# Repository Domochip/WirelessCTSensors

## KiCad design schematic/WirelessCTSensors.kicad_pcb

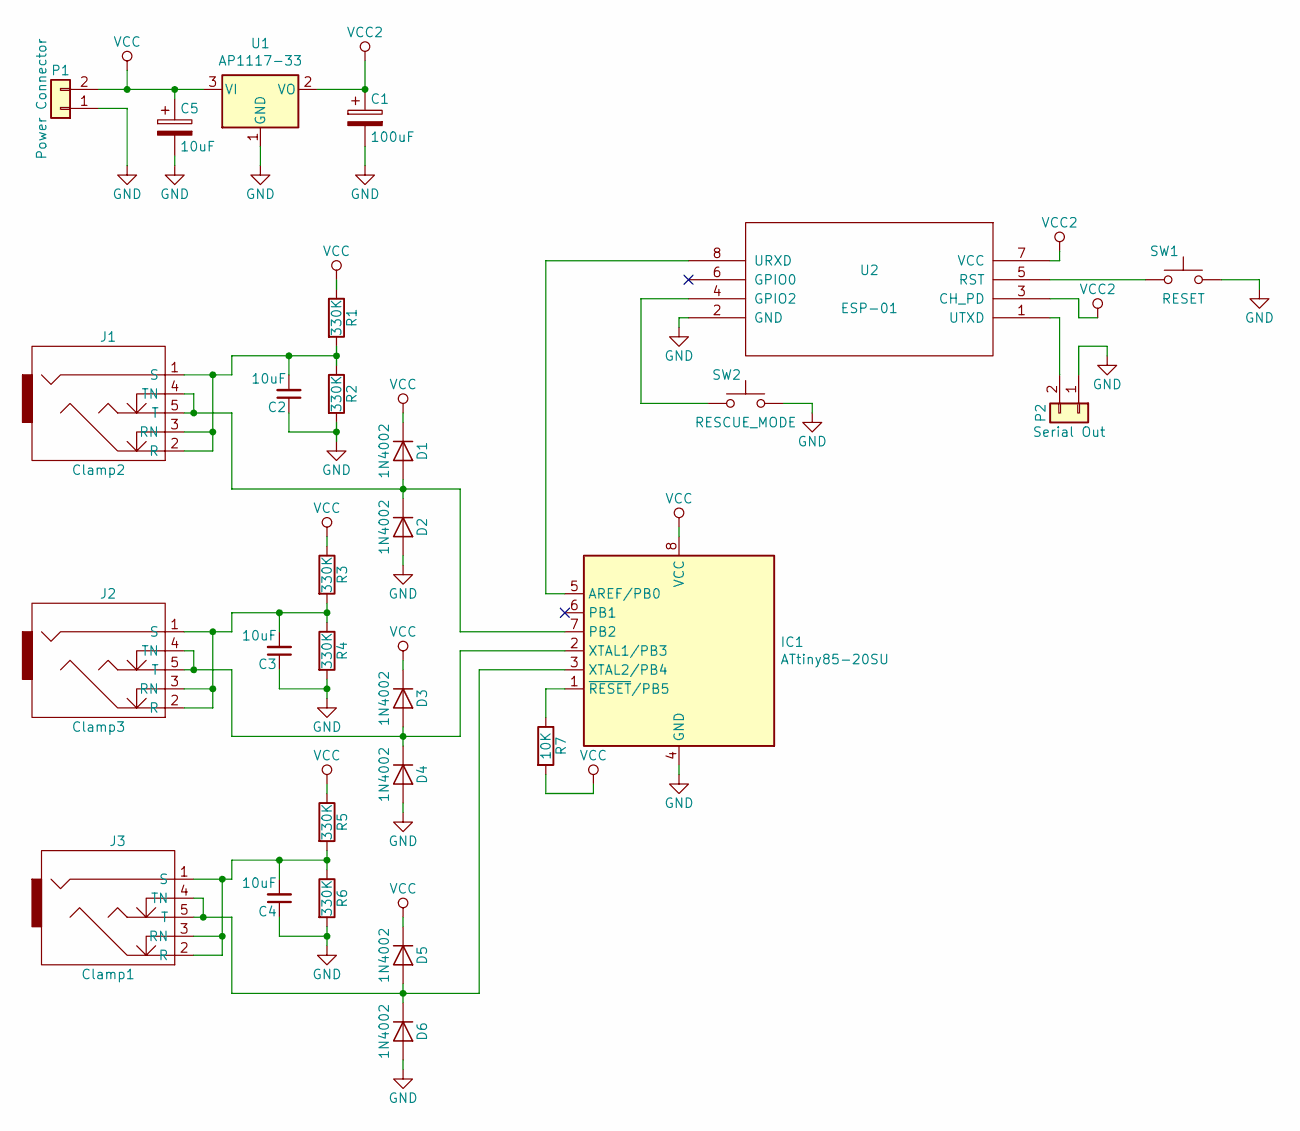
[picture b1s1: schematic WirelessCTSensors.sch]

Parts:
C1: 100uF; TantalC_SizeB_EIA-3528_HandSoldering
C2, C3, C4: 10uF; C_0805_HandSoldering
C5: 10uF; TantalC_SizeA_EIA-3216_HandSoldering
D1, D2, D3, D4, D5, D6: 1N4002; SMA_Handsoldering
IC1: ATtiny85-20SU; DIP-8_W7.62mm_LongPads
J1: Clamp2; jack_trs_5pins
J2: Clamp3; jack_trs_5pins
J3: Clamp1; jack_trs_5pins
P1: Power Connector; TerminalBlock_bornier-2_P5.08mm
P2: Serial Out; Pin_Header_Straight_1x02_Pitch2.54mm
R1, R2, R3, R4, R5, R6: 330K; R_0805_HandSoldering
R7: 10K; R_0805_HandSoldering
SW1: RESET; SW_PUSH_6mm
SW2: RESCUE_MODE; SW_PUSH_6mm
U1: AP1117-33; SOT-223
U2: ESP-01

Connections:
GND: C1.2, C2.1, C3.1, C4.1, C5.2, D2.2 (A), D4.2 (A), D6.2 (A), IC1.4 (GND), P1.1, P2.1, R2.2, R4.2, R6.2, SW1.2, SW2.2, U1.1 (GND), U2.2 (GND)
unnamed: C2.2, J1.1 (S), J1.2 (R), J1.3 (RN), R1.2, R2.1
unnamed: C3.2, J2.1 (S), J2.2 (R), J2.3 (RN), R3.2, R4.1
unnamed: C4.2, J3.1 (S), J3.2 (R), J3.3 (RN), R5.2, R6.1
unnamed: D1.2 (A), D2.1 (K), IC1.7 (PB2), J1.4 (TN), J1.5 (T)
unnamed: D3.2 (A), D4.1 (K), IC1.2 (XTAL1/PB3), J2.4 (TN), J2.5 (T)
unnamed: D5.2 (A), D6.1 (K), IC1.3 (XTAL2/PB4), J3.4 (TN), J3.5 (T)
unnamed: IC1.1 (~RESET~/PB5), R7.1
unnamed: IC1.5 (AREF/PB0), U2.8 (URXD)
unnamed: P2.2, U2.1 (UTXD)
unnamed: SW1.1, U2.5 (RST)
unnamed: SW2.1, U2.4 (GPIO2)
VCC: C5.1, D1.1 (K), D3.1 (K), D5.1 (K), IC1.8 (VCC), P1.2, R1.1, R3.1, R5.1, R7.2, U1.3 (VI)
VCC2: C1.1, U1.2 (VO), U2.3 (CH_PD), U2.7 (VCC)

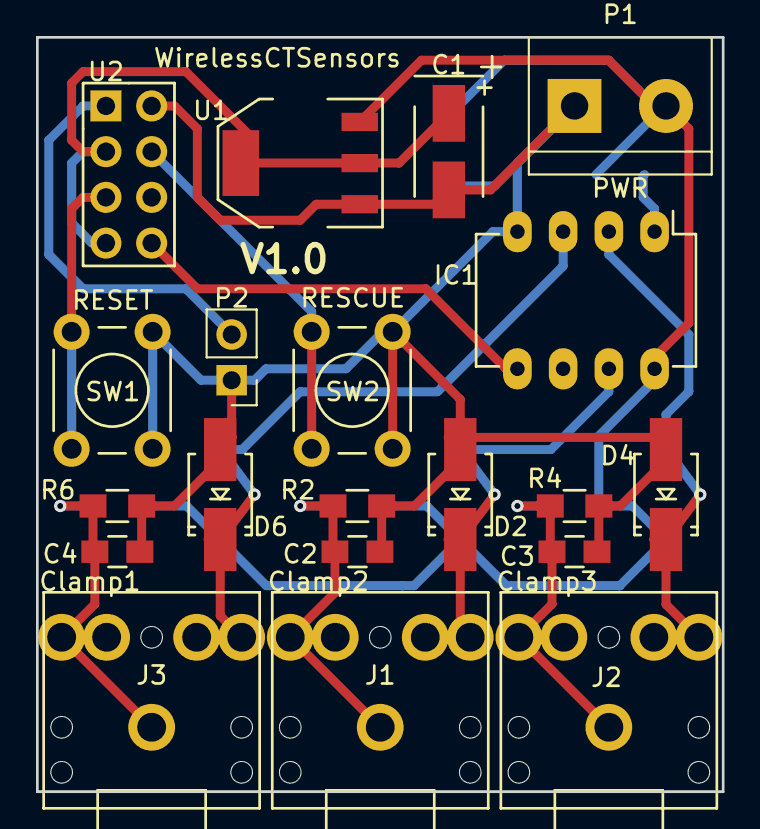
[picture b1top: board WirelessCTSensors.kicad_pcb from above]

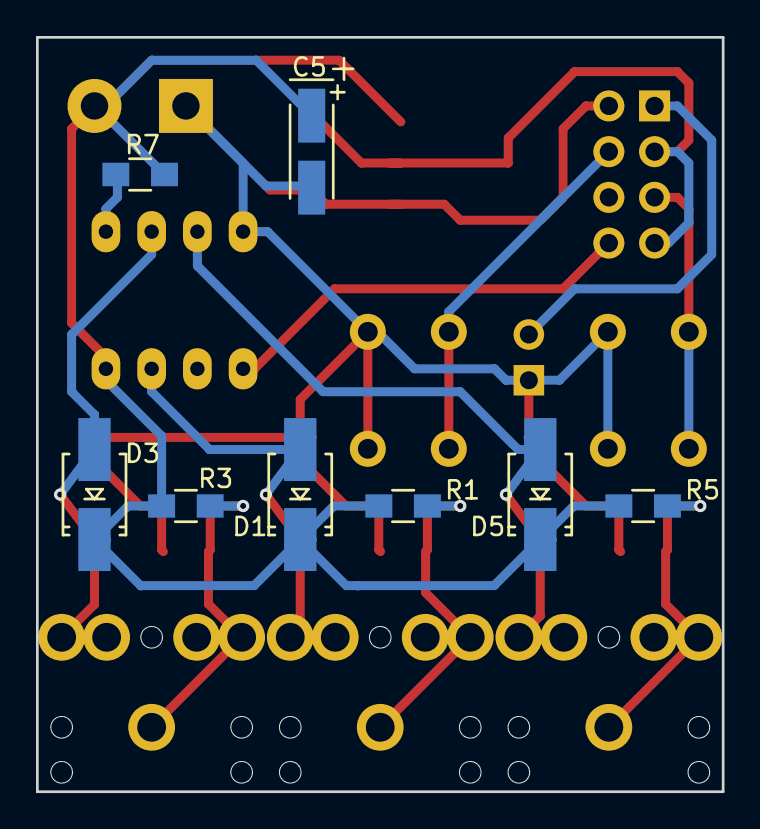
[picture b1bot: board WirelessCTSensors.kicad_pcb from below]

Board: 2 copper layers, 38.1 x 41.9 mm, 28 parts (8 on the bottom side), 14 nets.

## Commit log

2018-03-13 V3.1.3 Initial Commit
2018-03-24 Update according to Base v1.0.5 + v3.1.4
    3.1.4 add Reset Method to CTSensor for app Reinit
2018-04-03 V3.1.5 Change Data Structure
    Data structure evolved in order to support other Home Automation system
2018-05-22 Switch to PlatformIO
2018-06-20 Switch to Base v1.0.10
2018-06-20 Add rename script to PlatformIO
2018-10-26 Switch to Base V1.1.5
2018-11-17 Switch to Base V1.1.6
    - No More PowerShell
    - GZIP and convertion to header done in python with platformIO
    - Webpages small improvement
2018-11-27 Fix base
2019-03-17 V3.1.6 Upgrade to Base V1.1.7
2019-04-07 PureCSS Fix because of GIT AutoCRLF Windows users enable autocrlf by default, and so pure-min.css crlf modified make bad integrity check
2019-04-13 Improved copy_base.py
2019-04-13 V3.1.7 Replace SimpleTimer by Ticker
2019-08-12 Update gitignore
2019-09-15 V3.2.0 Add MQTT / Remove HTTP Jeedom
    Due to Jeedom evolution, We can't anymore request virtual values.
    Switch to MQTT protocol using retain flag on counter to be able to get it back at reboot
2019-10-13 Compatibility with Python3
2019-11-15 Up to base V1.3.0
2019-11-17 Up to Base V1.3.1
2019-11-17 Base fix
2019-11-18 Up to Base V1.3.2
2019-11-22 Up to base V1.3.3
2019-11-23 Naming Convention
2019-11-27 Log AP Name
2020-01-12 Update schematic
2020-11-01 Up to base V1.4.0 /!\ Configuration lost after flash /!\
